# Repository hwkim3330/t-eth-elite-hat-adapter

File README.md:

# T-ETH-Elite ↔ Raspberry Pi HAT adapter

Hardware that lets a **Raspberry Pi HAT** run on a **LilyGO T-ETH-Elite**
(ESP32-S3) instead of a Pi. Built for one specific HAT — TSN Lab's
`10BASE-T1S HAT` (Microchip LAN8651, [devicemart #15980354](https://www.devicemart.co.kr/goods/view?no=15980354)),
which is a Pi-only product — so that a 10BASE-T1S node can be an ESP32 rather
than a Raspberry Pi. Firmware side lives in
[esp32-t1s-bridge](https://github.com/hwkim3330/esp32-t1s-bridge).

```
   TSN Lab 10Base-T1S HAT  (LAN8651)
   ── adapter PCB ──                    pcb/
   LilyGO T-ETH-Elite  (ESP32-S3)
   ── printed tray ──                   case/
```

| | |
|---|---|
| `pcb/` | the adapter board — KiCad project, gerbers, BOM/CPL |
| `case/` | printed base tray for the Elite, generated and clearance-checked by script |
| `reference/` | LilyGo's own DXF and 3D models, plus the script that re-derives every dimension from them |
| [`pcb/GEOMETRY.md`](pcb/GEOMETRY.md) | **the single source of truth** — every measured number, with its provenance |

## The short version of why this exists

Plugging the HAT straight onto the T-ETH-Elite *almost* works, and the two
reasons it doesn't are worth stating up front:

1. **Electrically it already works.** LilyGo wired the Elite's 40-pin header to
   the standard Raspberry Pi GPIO assignment, pin for pin. No level shifting,
   no remapping, nothing to translate. The adapter carries no signal logic at
   all — the connection is the stacking header's own pins, straight through.
2. **The near mounting holes already line up.** Deriving where a Pi's
   header-end holes must sit, from the Elite's own header position, lands on
   the Elite's own bottom hole pair to within **0.005 mm**. Same holes.
3. **But the RJ45 is in the way.** The Elite's RJ45 stands **15.97 mm** off the
   PCB while its header pins stop at **10.10 mm**. Any flat, un-notched board
   dropped onto that header — which is exactly what a standard Pi HAT is — hits
   the jack 5.87 mm before it seats. LilyGo's own shields cut a notch for it.
4. **And the far mounting holes fall off the end.** A HAT's far holes sit 49 mm
   from the near pair, i.e. at y = 53.63 in the Elite's frame — past the Elite's
   own board edge at 49.19. There is nothing there to screw into.

Of those, only (4) genuinely needs a board. A tall enough stacking header would
lift a HAT clear of the RJ45 on its own — so the honest claim is not "a HAT
cannot sit on this board", it is that without the adapter a HAT sits on **two
screws at the connector end and nothing at the other**, with the Elite's BOOT
and RESET switches buried underneath it. On a board you push terminal-block
levers into, that is the difference between a fixture and a wobble.

## Provenance

Nothing here was scaled off a drawing by eye. The mounting holes, the 40-pin
grid, the outline notches and the component heights all come out of LilyGo's own
published DXF and 3D CAD, cross-checked three ways — and the hole pattern was
independently validated against a real board on a laser-cut plate in
`~/stl-model/acrylic-frame`. `reference/measure.py` re-derives the whole set
from the vendor files, so the numbers can be audited rather than trusted:

```bash
pip install --user ezdxf trimesh manifold3d py7zr
python3 reference/measure.py
```

The one number that is *not* from CAD is the HAT's own 58 × 49 hole pattern,
which is inferred from a product photo (method and error bars in
[`pcb/GEOMETRY.md`](pcb/GEOMETRY.md)). Only the placement of the adapter's two far holes depends
on it.

## Status

Designed, checked, **never built**. No board has been fabricated, nothing has
been printed, and no part of the stack has been assembled or powered. The
clearance check the case script runs is against LilyGo's model, not against a
real board. Read the "not verified" sections in [`pcb/README.md`](pcb/README.md) and
[`case/README.md`](case/README.md) before spending money.

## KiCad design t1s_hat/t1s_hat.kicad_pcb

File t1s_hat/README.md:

# T1S HAT — LAN8651 10BASE-T1S for the LilyGO T-ETH-Elite

Our own 10BASE-T1S board for the [LilyGO
T-ETH-Elite](https://github.com/Xinyuan-LilyGO/LilyGO-T-ETH-Series)
(ESP32-S3), built around a **Microchip LAN8651** MAC-PHY. It replaces buying
TSN Lab's ready-made HAT: same chip, same host header, our schematic.

Two source files govern this board and **nothing here re-derives a number in
either of them**:

| file | governs |
|---|---|
| [`ELECTRICAL.md`](ELECTRICAL.md) | every component, value and pin-handling rule, each quoted from Microchip DS60001734F or AN1718 (DS60001718D) |
| [`../pcb/GEOMETRY.md`](../pcb/GEOMETRY.md) | outline, mounting holes, 2×20 grid — measured from LilyGo's own DXF and 3D CAD |

Everything is generated by [`make_t1s_hat.py`](make_t1s_hat.py), which emits
the symbol library, the two project-local footprints, the schematic and the
PCB, then reads the board back and asserts every mechanical feature against
`GEOMETRY.md`.

## What it is

- **LAN8651**, 32-VQFN 5×5, single 3.3 V rail (the '51 regulates its own 1.8 V
  core, so there is no second regulator and no sequencing diode).
- **OPEN Alliance TC6 SPI** to the host on the same header pins TSN Lab's
  device-tree overlay uses, so their SDK and the mainline `microchip,lan8651`
  driver both work unmodified if this board is ever put on a Pi.
- **Bus interface network** in AN1718's MINIMAL BIN order: common-mode choke →
  AC coupling caps → termination → ESD → 4-way 3.81 mm pluggable terminal
  block, wired so the node taps a daisy chain.
- 38 parts, 4 of them deliberately unstuffed. One of the 38 is a 0 Ω jumper,
  and it is a design decision, not an accident — see below.

## The two parts that had to be chosen, not assumed

Both are drawn from their own data sheet into
[`fp/t1s_hat.pretty`](fp/t1s_hat.pretty), generated by `make_t1s_hat.py`
alongside the board, and the generator asserts the pad count and the overall
land size back out of the finished `.kicad_pcb`.

### L1 — TDK **ACT1210L-201-2P-TL00**, LCSC **C131444**

AN1718 names ACT1210D-131-2P-TL00, ACT1210E-241-2P-TL00 and Murata
DLW32MH241MX2, and says in the same breath that *"exact component part numbers
and parameters must be determined by the customer's unique application
requirements"* — they are examples. All three are **3.2 × 2.5 mm** (EIA 1210)
2-line chokes in the 130…240 µH @ 100 kHz band. The board previously sat on
KiCad's `Inductor_SMD:L_CommonMode_Wurth_WE-CNSW-1206`, a **3.2 × 1.6 mm**
land: same length, 0.9 mm too narrow, so the real part's terminals miss the
pads. KiCad ships no 4-terminal common-mode choke land in 3225.

The part fitted instead is the **ACT1210L-201-2P-TL00**: same ACT1210 package,
200 µH @ 100 kHz — inside the span AN1718's own examples cover — 70 mA,
5.5 Ω, AEC-Q200, and, unlike all three examples, **stocked at LCSC**
(C131444, ~$0.39/1k), which is where this board gets built.

Its land is `t1s_hat:L_CommonMode_TDK_ACT1210_3225`, drawn from TDK's ACT1210
data sheet "Layout recommendation" (drawing IND1512-9): **4.1 mm overall
across the pads with a 2.0 mm gap between the columns**, so each pad is
1.05 mm long on a 3.05 mm pitch, and **1.6 mm overall across the rows with a
0.4 mm gap**, so each pad is 0.60 mm wide on a 1.0 mm pitch. Body from the
same sheet: 3.2 ±0.2 long, 2.5 ±0.2 wide, 3.9 max over the terminals.

The symbol changed with it: the ACT1210's windings are **1-4 and 2-3**
(pin configuration and circuit diagram, same sheet), which is
`Device:L_Coupled_1423`, not the `…_1243` the 1206 Würth part needed.

### MOV1 / MOV2 — TDK **AVRH10C221KT1R5YA8**, LCSC **C2157827**

This is the part `ELECTRICAL.md` already names, and it is a **1005 [0402]**
chip varistor — 1.0 × 0.5 × 0.5 mm, 220 V V1mA, 70 V DC, **1.5 pF**, 25 kV per
IEC 61000-4-2. The board had it on `Resistor_SMD:R_1206_3216Metric`: three
size codes too big. It is now on `t1s_hat:Varistor_TDK_AVRH10_1005`, from the
recommended land pattern in TDK's automotive AVR chip-varistor catalogue
(pad 0.35…0.45 long, gap 0.3…0.5, pad 0.4…0.6 wide — the middle of each:
**0.40 long, 0.40 gap, 0.50 wide**). KiCad's `R_0402_1005Metric` is 0.54 ×
0.64 on a 1.02 mm pitch, outside all three ranges, which is why this one is
drawn here too. Both parts stay **DNP**; the land is now a real one.

## Three decisions that are not in ELECTRICAL.md / GEOMETRY.md

These were directed after those files were written. They are marked
`DIRECTED:` in the generator, and the reasoning is recorded here.

### 1. Two layers, not four

`ELECTRICAL.md` calls 4 layers non-negotiable because AN1718 wants TRXP/TRXN
as length-matched, impedance-controlled 50 Ω single-ended traces, and 50 Ω on
2-layer 1.6 mm FR4 needs a ~2.9 mm trace. The width figure is right; the
conclusion does not follow at this speed and length. 10BASE-T1S runs at
12.5 MBd with deliberately slow, EMC-shaped edges, and the run from the QFN to
the connector here is ~20 mm — electrically short, well under the length at
which a mismatch on a trace this short costs anything at these edge rates.
AN1718's 50 Ω line is a "do this and you are safe" recommendation, not a
threshold this design crosses.

**So the impedance is not controlled and is not claimed to be.** The pair is
0.35 mm over 1.51 mm of FR4, which is nowhere near 50 Ω. What buys the margin
back instead is layout discipline, and those rules are treated as hard:

- **All signal routing is on F.Cu. B.Cu is an uninterrupted ground pour.**
  The generator asserts this — `verify()` counts B.Cu tracks and the table
  prints `B.Cu signals … 0 tracks`.
- The only two interruptions in that plane are the antenna keepout and the
  all-layer void under the choke, both of which AN1718 or the Elite requires,
  and the choke void is sized to the choke — see inference 8.
- The one crossing that a single signal layer could not absorb is a **0 Ω
  jumper on F.Cu**, not a via pair through the plane. See below.
- TRXP/TRXN are short, symmetric about x = 29.0 from the QFN to the connector,
  and carry **no vias**.

Moving to 4 layers with a dedicated reference plane is the fallback if EMC
measurements later ask for it. It is not a cost compromise.

### 2. No RJ45 notch — the outline is a plain rectangle

`GEOMETRY.md`'s notch exists because a board ~13 mm above the Elite would foul
the RJ45, which stands 15.97 mm. This board is lifted clear of the jack by a
taller riser instead, so nothing has to be cut away. Outline is the full
**66.22 × 49.19 mm rectangle, 3 mm corners**. Everything else mechanical in
`GEOMETRY.md` is unchanged and still authoritative: the four asymmetric
mounting holes and the 2×20 grid.

That is also what makes the 2-layer decision work — the notch was the largest
interruption in the bottom-side ground pour, right where the pair and its
choke want a clean reference.

### 3. The connection is two-stage — read this before ordering parts

```
   T1S HAT  (this board)
        ↑ its 2x20 socket goes on the riser's long pins
   ── 2x20 stacking riser ──          ≈18-20 mm total, set by the riser
        ↑ riser socket swallows the Elite's own 9.30 mm pins
        ↑ RJ45 (15.97 mm) passes beside the stack, not through a notch
   LilyGO T-ETH-Elite (ESP32-S3)
```

**A single tall stacking header does not work here.** The Elite's pins are
only 9.30 mm long; they would reach barely halfway up a ~17 mm barrel whose
contacts sit near the top. You need a **riser** (a 2×20 stacking header that
plugs onto the Elite and presents longer pins) plus this board's **socket**.
That is a real failure mode someone will otherwise hit at the checkout page.

Board height above the Elite PCB is **assumed ≈18–20 mm**, set by the riser.
Nothing on this board depends on the exact number.

## Stack-up assumed

JLCPCB's standard 2-layer 1.6 mm FR4 build, written into the board file:

| layer | | thickness |
|---|---|---|
| F.Cu | signals + GND flood | 0.035 mm (1 oz) |
| core | FR4, εr ≈ 4.5 | 1.510 mm |
| B.Cu | **ground plane, nothing else** | 0.035 mm (1 oz) |

Design rules: 0.15 mm minimum clearance and track, 0.45 mm minimum via
(0.25 mm drill), 0.20 mm minimum through-hole drill — the last one because the
stock `…_ThermalVias` QFN footprint uses 0.20 mm holes under the exposed pad.

## Termination stuffing — the one thing an assembler must decide

The board **ships with R1/R2 unstuffed**, per `ELECTRICAL.md` ("footprints
fitted, DNP by default — stuff per where this node sits on the bus"). The
silkscreen carries the table:

| where this node sits | R1, R2 |
|---|---|
| **end of the bus** | 49R9 1 % 1 W 1206 |
| **interior drop node** | 1K5 1 % 1206 |

`R3` (100 k) and `C3` (100 nF) — AN1718's common-mode termination — **are
fitted**. ESD elements MOV1/MOV2 have footprints and are DNP; `ELECTRICAL.md`
calls them optional.

`CN1` is wired **P N N P**, and the silkscreen carries that as a legend
(`CN1 1=P 2=N 3=N 4=P`) in the clear area to its left. Per-pad letters were
dropped: the four pads are 1.8 × 3.6 mm ovals with the connector's own body
outline 0.9 mm below them and R3/C3 0.6 mm below that, leaving a 0.6 mm slot —
nowhere to letter a pad without printing on copper. Pins 1–2 and 3–4 are the
same pair with opposite orientation, so wire P to P and N to N rather than
pin-for-pin. That order is what lets both on-board links be drawn without a
crossing.

## Verified

- **Mechanical: worst error 0.00000 mm** against `GEOMETRY.md`, tolerance
  0.01 mm, over the outline, all four mounting holes and all 40 header pads.
  `make_t1s_hat.py` prints the full table and exits non-zero on any failure.
- **Antenna keepout clean.** The generator walks every track, via, footprint
  and *filled zone polygon* on both layers and counts anything inside
  x 58…66.22, y 22…44: **0 intruders.** The keepout is a rule area that forbids
  copper, tracks, vias, pads and footprints on both layers, so both pours are
  cut out there. Silkscreen (ink, not copper) does mark the window.
- **B.Cu carries 0 signal tracks.**
- **Unrouted connections: 0.**
- **L1 and MOV1/MOV2 lands read back as 4.10 × 1.60 mm on 4 pads and
  1.20 × 0.50 mm on 2 pads** — the data sheet numbers above, asserted out of
  the board file, not just written into it.
- **ERC: 0 errors, 5 warnings** — see below.
- **DRC: 0 errors, 4 warnings** — see below.

### ERC — 0 errors

`kicad-cli` 7.0.11 has no `sch erc` subcommand, only `export`, so ERC is run
through the real eeschema on an Xvfb display by
[`run_erc.sh`](run_erc.sh), with **Show: All and Exclusions both ticked**
before the run. Report as produced: [`erc.rpt`](erc.rpt).

```
** ERC messages: 5  Errors 0  Warnings 5
```

All 5 warnings are the same thing: *"Pins of type Bidirectional and Power
output are connected"* on U1 pins 20, 22, 23 (DIOA2/3/4) and 16, 14
(DIOB0/DIOB1). Those are the unused configurable IO tied to ground, which is
exactly what the data sheet says to do — *"When not used, these pins may be
connected directly to ground."* Nothing is excluded or suppressed.

### DRC — 0 errors, 4 warnings

Run through `pcbnew.WriteDRCReport()` (same engine; `kicad-cli` has no
`pcb drc` either). Report as produced: [`drc.rpt`](drc.rpt).

```
** Found 4 DRC violations **
** Found 0 unconnected pads **
** Found 0 Footprint errors **
```

**Zero errors of any kind** — no clearance, hole, courtyard, keepout,
solder-mask, silkscreen or unconnected-pad violation. All four remaining
warnings are the same one:

| count | what |
|---|---|
| 4 | `lib_footprint_issues` — the four Ø2.75 mounting holes are generated inline and belong to no footprint library, so the library-consistency test has nothing to compare them to (same as `../pcb/`) |

Nothing is excluded. Running it yourself reproduces exactly this.

## Two crossings on one layer, and how they were closed

The host bundle is **not planar on one layer**. With the LAN8651's pin order
(IRQ 9, SDO 10, CS_N 11, SCLK 12, SDI 13, left to right along the QFN's bottom
edge) and `ELECTRICAL.md`'s header assignment (IRQ→16, MOSI→19, MISO→21,
SCLK→23, CS_N→24), SDI/MOSI starts at the right-hand end of the QFN and has to
reach the left-hand end of its target group, so it must cross the other four.
MOSI takes the long way round — out to x = 39.9, down, and back along a 2 mm
band under the header — which resolves that crossing, but the loop it traces
then encloses the CS_N column, and 3V3 enters the board outside that loop.
VDDP is fenced in the same way, by the +3V3 tree, the header row and the SPI
fan-out. That left one crossing on each of two nets.

**B.Cu was not used for either.** The uninterrupted bottom pour is the thing
buying back the fourth layer on this design; `B.Cu signal tracks: 0` is still
asserted by the generator and still true.

### `SPI_CS_N` — closed by moving R5, no new part

R5 (the 10 k CS_N pull-up) moved from (50, 12.4) to **(32.326, 9.5)**, where it
sits **astride the SPI_MISO column**: MISO runs vertically between R5's own two
pads. A 0603's pads are 0.85 mm apart, so a 0.25 mm track through the middle
keeps 0.30 mm to each — the textbook 2-layer crossover, except that the part
doing the hopping is one that had to be in the CS_N path anyway. Its 3V3 now
comes off the column that already feeds R6, and its CS_N leg lands straight on
the CS_N column. Cost: zero extra parts.

### `VDDP` — closed by JP1, a real 0 Ω jumper

There is no equivalent trick for VDDP: its two halves are both VDDP, and no
VDDP-to-VDDP part existed to hop with. So **JP1, a 0 Ω 0603, is fitted at
(6.9, 8.7)**, straddling the +3V3 branch that climbs the left edge — +3V3
passes between its pads. It is a real part, and it is real everywhere:

- in the schematic, as `Device:R`, with the net split either side of it
  (`VDDP` on the pin-7 island, **`VDDP_17`** on the pin-17 island, each with
  its own PWR_FLAG so ERC sees both as supplied);
- in [`bom.csv`](bom.csv) and [`cpl.csv`](cpl.csv), `Populate = fit`, described
  as *"FITTED — the board does not work without it"*;
- on the silkscreen, designator `JP1`, like every other part.

From JP1 the link runs round the outside of the header in the free ~1 mm lane
below it and climbs back between two pad columns at x = 42.486. Nothing else
goes under the header there: the +3V3 rail stops at y = 2.0 and MOSI's return
at y = 1.35, and both turn upward before that lane. It is a long way round —
the VDDP_17 net totals 84 mm of 0.30…0.45 mm track, about 0.1 Ω, ~3 mV at
50 mA — and each island keeps its own 0.1 µF + 0.01 µF at the pin, so the
length costs nothing that matters. **The short way round does not exist on one
layer**; the alternative was a via pair through the ground plane, which this
design does not spend.

## Silkscreen — 48 violations to 0

The silkscreen exists so the board can be assembled and debugged, and it was
not doing that job: designators sat on pads and on each other (`R3` across the
connector, `C1`/`C2` over pads, `MOV2` into `CN1`).

| | before | after |
|---|---|---|
| `silk_overlap` | 28 | **0** |
| `silk_over_copper` | 15 | **0** |
| `silk_edge_clearance` | 5 | **0** |
| designators dropped | — | **0 of 38** |

Library footprints put their reference wherever the library author did, which
on a board this dense is wherever the neighbour already is. They are placed by
the generator instead: `place_references()` tries each designator in a ring of
candidate positions around its own part — horizontal first, sideways only if
nothing horizontal fits — and keeps the first that clears every pad, via, ink
and the board edge. A part with nowhere legible left would lose its
designator rather than print an unreadable pile; in the end none had to.
Three positions are hinted (`J1`, `U1`, `R1`, `Y1`) because the ring around a
large or boxed-in part lands somewhere silly, and a hint still has to pass the
same clearance test as any other candidate.

Four other things moved with it:

- **Board text** was re-laid into the two areas that carry no pads — the strip
  left of the bus network and the top-right corner — and shortened to fit
  clear of CN1's body outline.
- **CN1's per-pad P/N letters** became one legend line; see above.
- **The J1 pin-1 marker** is a filled dot outboard of pin 1, not a stroked
  triangle above it. Above is where JP1 has to sit, and the triangle's three
  legs also overlapped *each other* at the apex — one filled shape cannot.
- **CN1 moved 0.35 mm inboard** (y 41 → 40.65): its body outline otherwise
  lands 0.02 mm from `Edge.Cuts`, and the keepout window's ink now stops
  0.32 mm short of the board edge instead of running onto it.

## Inferences — things not taken from the spec files

Flagged because they are judgement, not quotation:

1. **U1 pin 1 (INH) is left unconnected.** `ELECTRICAL.md`'s pin-handling
   table does not cover INH. DS60001734F Table 3-5 says *"When not used, this
   pin should be left unconnected"*, so it is, with no copper stub.
2. **L1 is a 200 µH part where AN1718's examples are 130 and 240 µH.**
   AN1718 gives no minimum or maximum, only three example part numbers and an
   instruction to pick for the application; 200 µH is inside the span they
   cover and is the value TDK itself lists for one-pair automotive Ethernet.
   The land pattern is quoted, not inferred — but the *choice of value inside
   that span* is judgement.
3. **The 0 Ω jumper JP1 and the net split `VDDP` / `VDDP_17`** are a layout
   decision, not something either spec file asks for. `ELECTRICAL.md` treats
   VDDP as one net; on this board it is one net with a 0 Ω link in it.
4. **The crystal is a 2-pin 3.2 × 1.5 mm package** (`Crystal_SMD_3215-2Pin`),
   not a 4-pin grounded-case one. `ELECTRICAL.md` specifies 25 MHz,
   fundamental, parallel, CL 18 pF and says nothing about the package; the
   2-pin part routes cleanly here. A grounded-case 3225 is better for EMC and
   is a footprint swap.
5. **XTI is declared `passive` in the LAN8651 symbol**, not `input`. It is an
   oscillator pin driven by a passive crystal; declaring it an input makes
   KiCad's `pin_not_driven` test fire on a net that has no driver by design.
   Common practice, but it is a choice.
6. **The 40-pin header is a project-local symbol**, `t1s_hat:HAT_HEADER_2x20`,
   not `Connector_Generic:Conn_02x20_Odd_Even`. Its pins carry real electrical
   types (the six host signals are `output`/`input`, everything else
   `passive`), because the ESP32 side really is the driver and the generic
   connector's all-passive pins make ERC report every SPI input as undriven.
   The **footprint** is the stock `PinHeader_2x20_P2.54mm_Vertical`.
7. **Header pin 1 is at the low-x end, odd pins on the y = 3.360 row.**
   Inherited from `../pcb/`, where it is derived (not measured) from the Pi
   convention and from USB_DN/DP on pins 35/37 routing to the Elite's
   right-hand USB-C. Affects silkscreen only.
8. **`BIN_VOID` = x 21…40.5, y 23.4…39.8** and **`CMC_VOID` = x 26.90…30.10,
   y 24.40…28.80.** AN1718 asks for "a void in the ground flooding on the
   outside layer surrounding the BIN" and "an all-layer void underneath the
   CMC" **without giving dimensions**, so both sizes are judgement. The first
   follows the BIN components. The second is the only place other than the
   antenna window where the B.Cu reference plane is cut, so it is sized to the
   part and no further: **the ACT1210's maximum body — 3.9 mm over the
   terminals × 2.7 mm wide (2.5 + tolerance) — plus 0.25 mm a side**, giving
   3.2 × 4.4 mm (L1 is rotated 90°, so the 3.9 runs along y). The margin
   covers placement tolerance and nothing else; the body is what couples to
   the plane, because the body is the core. That also covers the 4.1 × 1.6 mm
   land with room to spare. The void grew in x against the old number above,
   not because the margin grew but because the part did: the 1206 land it used
   to be sized around was the wrong part. C11/C12 moved 0.8 mm outboard so
   their ground vias stay clear of it.
9. **The T1S pair necks to 0.15 mm at the QFN.** The package puts TRXP and
   TRXN 0.5 mm apart; AN1718's "3× trace width centre-to-centre to other
   signals" cannot be met between the pair's own two legs at a 0.5 mm-pitch
   QFN, and Microchip's own EVB does not either. It **is** met against every
   other net, by the F.Cu void around the BIN.
10. **Pair length match ≈0.2 mm.** TRXN opens out to the choke before TRXP
    does (so the gap only ever grows), which costs about 0.2 mm of mismatch —
    roughly 1.2 ps. Not measured on hardware.
11. **The stackup numbers** (1.51 mm core, εr 4.5, 1 oz outer copper) are
    JLCPCB's standard 2-layer build, taken as the assumption, not measured.

## Files

| file | what |
|---|---|
| `ELECTRICAL.md` | **electrical source of truth** |
| `make_t1s_hat.py` | generator: symbol lib → schematic → PCB → verify → DRC → exports |
| `run_erc.sh` | runs eeschema's ERC headlessly (Xvfb + xdotool) and saves the report |
| `fill_zones.sh` | fills the zones through pcbnew's GUI — `ZONE_FILLER` segfaults in KiCad 7.0.11's Python bindings |
| `t1s_hat.kicad_sch` / `.kicad_pro` / `sym-lib-table` / `fp-lib-table` | schematic + project |
| `sym/t1s_hat.kicad_sym` | **LAN8651** (33 pins incl. the exposed pad) and the host header — neither exists in KiCad's libraries |
| `fp/t1s_hat.pretty/` | the TDK ACT1210 choke land and the TDK AVRH10 varistor land, each from that part's own data sheet — KiCad ships neither |
| `t1s_hat.kicad_pcb` | the board |
| `gerbers/t1s_hat_gerbers.zip` | fab-ready: 8 gerber layers, separate PTH/NPTH Excellon, drill maps, job file |
| `bom.csv` / `cpl.csv` | BOM (with a `Populate` column) and position file |
| `preview-front.png/.svg`, `preview-back.png/.svg` | both sides |
| `erc.rpt` / `drc.rpt` | reports as produced, nothing excluded |

Regenerate with `python3 make_t1s_hat.py`. Geometry is reproducible to the
internal unit, but the output is not byte-reproducible — KiCad stamps fresh
UUIDs and timestamps on every run. Compare the printed coordinate table, not
the files.

Drill files and `cpl.csv` are plotted against the drill/place origin, which the
generator puts on `GEOMETRY.md`'s own origin, so `NPTH.drl` literally reads
`X3.33Y4.63` and `cpl.csv` reads `8.196, 3.360`.

## Bottom side — clear area for a later variant

The board now sits ~18–20 mm above the Elite, so **the bottom is usable**:

| region | clearance below |
|---|---|
| everywhere except the RJ45 footprint | ≈14 mm or more |
| over the RJ45, x −5.18…16.42, y 10.50…28.90 | **much less** — the jack tops out at 15.17 mm above the Elite's PCB |
| under the 2×20 socket, y 0…9 | occupied by the socket body |

Nothing is placed on B.Cu on this board (it is the ground plane). A radar
variant wanting that space should stay clear of the RJ45 column and of the
header, and must not slot the plane under the bus pair.

## What is NOT verified — read before ordering

- **Nothing has been bench-tested.** No board, no Elite, no riser in hand.
- **The two project-local lands are transcribed from data sheets, not
  measured.** L1's came from TDK's ACT1210 layout recommendation and MOV's
  from TDK's AVR catalogue; the generator asserts that what is in the board
  file matches what was transcribed, which is not the same as asserting that
  the transcription is right. Both are worth one look at the PDF before fab —
  they are the only two lands here that KiCad did not supply.
- **LCSC stock and part status were read from the catalogue, not ordered
  against.** C131444 (L1) and C2157827 (MOV1/2) were in stock when this was
  written; neither is confirmed as a JLCPCB *basic* part, so expect an
  extended-part fee or hand-placement for L1.
- **Impedance is not controlled** and the 50 Ω figure in `ELECTRICAL.md` is
  deliberately not met; see the 2-layer decision.
- **Oscillator margin was not calculated.** `ELECTRICAL.md` asks for >10; that
  depends on the crystal's ESR and C0, which are not fixed to a part number.
- **The riser is specified by class, not part number**, and it sets the stack
  height. Pick it before the standoffs.
- **No order was placed.** The deliverable is fab-ready files to upload.

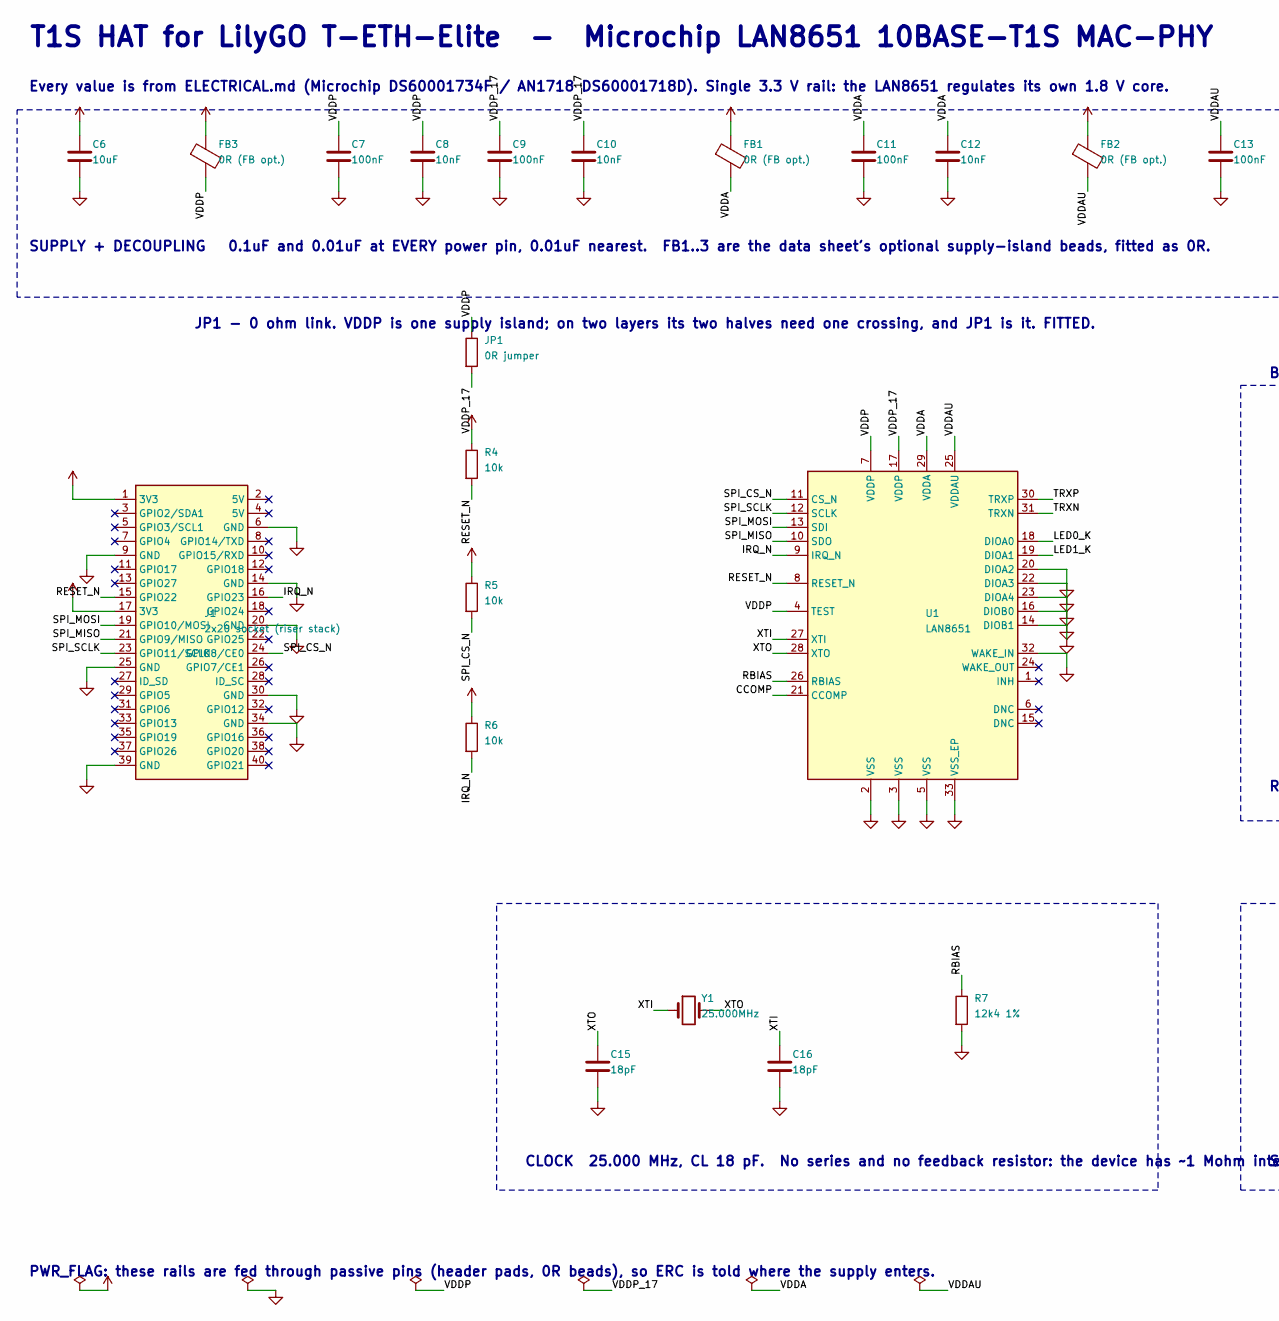
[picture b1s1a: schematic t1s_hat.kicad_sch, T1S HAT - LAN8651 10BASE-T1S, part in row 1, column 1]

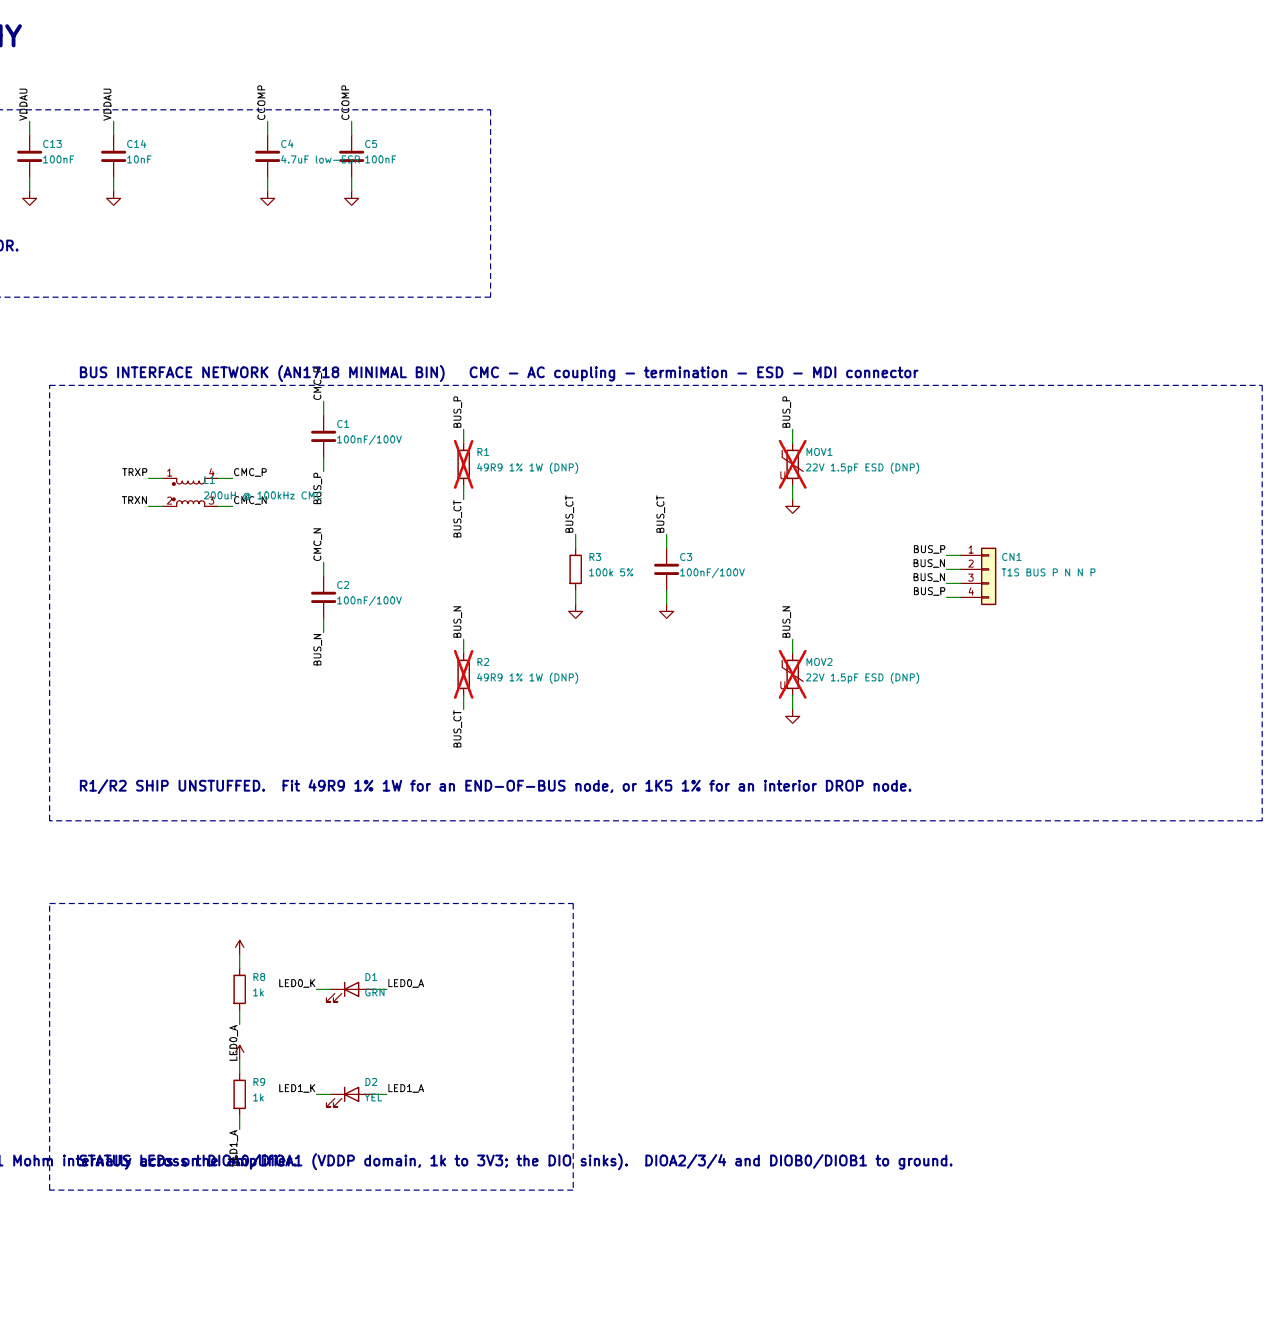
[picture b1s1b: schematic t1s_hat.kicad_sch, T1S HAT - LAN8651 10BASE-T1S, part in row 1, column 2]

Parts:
C1, C2, C3: 100nF/100V; C_0805_2012Metric
C4: 4.7uF low-ESR; C_0805_2012Metric
C5, C7, C9, C11, C13: 100nF; C_0603_1608Metric
C6: 10uF; C_0805_2012Metric
C8, C10, C12, C14: 10nF; C_0603_1608Metric
C15, C16: 18pF; C_0603_1608Metric
CN1: T1S BUS P N N P; PhoenixContact_MC_1,5_4-G-3.81_1x04_P3.81mm_Horizontal
D1: GRN; LED_0603_1608Metric
D2: YEL; LED_0603_1608Metric
FB1, FB2, FB3: 0R (FB opt.); L_0603_1608Metric
J1: 2x20 socket (riser stack); PinHeader_2x20_P2.54mm_Vertical
JP1: 0R jumper; R_0603_1608Metric
L1: 200uH @ 100kHz CMC; L_CommonMode_TDK_ACT1210_3225; LCSC C131444
MOV1, MOV2: 22V 1.5pF ESD (DNP); Varistor_TDK_AVRH10_1005; LCSC C2157827; not fitted
R1, R2: 49R9 1% 1W (DNP); R_1206_3216Metric; not fitted
R3: 100k 5%; R_0805_2012Metric
R4, R5, R6: 10k; R_0603_1608Metric
R7: 12k4 1%; R_0603_1608Metric
R8, R9: 1k; R_0603_1608Metric
U1: LAN8651; TQFN-32-1EP_5x5mm_P0.5mm_EP3.4x3.4mm_ThermalVias
Y1: 25.000MHz; Crystal_SMD_3215-2Pin_3.2x1.5mm

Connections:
+3V3: C6.1, FB1.1, FB2.1, FB3.1, J1.1 (3V3), J1.17 (3V3), R4.1, R5.1, R6.1, R8.1, R9.1
BUS_CT: C3.1, R1.2, R2.2, R3.1
BUS_N: C2.2, CN1.2, CN1.3, MOV2.1, R2.1
BUS_P: C1.2, CN1.1, CN1.4, MOV1.1, R1.1
CCOMP: C4.1, C5.1, U1.21 (CCOMP)
CMC_N: C2.1, L1.3
CMC_P: C1.1, L1.4
GND: C3.2, C4.2, C5.2, C6.2, C7.2, C8.2, C9.2, C10.2, C11.2, C12.2, C13.2, C14.2, C15.2, C16.2, J1.6 (GND), J1.9 (GND), J1.14 (GND), J1.20 (GND), J1.25 (GND), J1.30 (GND), J1.34 (GND), J1.39 (GND), MOV1.2, MOV2.2, R3.2, R7.2, U1.2 (VSS), U1.3 (VSS), U1.5 (VSS), U1.14 (DIOB1), U1.16 (DIOB0), U1.20 (DIOA2), U1.22 (DIOA3), U1.23 (DIOA4), U1.32 (WAKE_IN), U1.33 (VSS_EP)
IRQ_N: J1.16 (GPIO23), R6.2, U1.9 (IRQ_N)
LED0_A: D1.2 (A), R8.2
LED0_K: D1.1 (K), U1.18 (DIOA0)
LED1_A: D2.2 (A), R9.2
LED1_K: D2.1 (K), U1.19 (DIOA1)
RBIAS: R7.1, U1.26 (RBIAS)
RESET_N: J1.15 (GPIO22), R4.2, U1.8 (RESET_N)
SPI_CS_N: J1.24 (GPIO8/CE0), R5.2, U1.11 (CS_N)
SPI_MISO: J1.21 (GPIO9/MISO), U1.10 (SDO)
SPI_MOSI: J1.19 (GPIO10/MOSI), U1.13 (SDI)
SPI_SCLK: J1.23 (GPIO11/SCLK), U1.12 (SCLK)
TRXN: L1.2, U1.31 (TRXN)
TRXP: L1.1, U1.30 (TRXP)
VDDA: C11.1, C12.1, FB1.2, U1.29 (VDDA)
VDDAU: C13.1, C14.1, FB2.2, U1.25 (VDDAU)
VDDP: C7.1, C8.1, FB3.2, JP1.1, U1.4 (TEST), U1.7 (VDDP)
VDDP_17: C9.1, C10.1, JP1.2, U1.17 (VDDP)
XTI: C16.1, U1.27 (XTI), Y1.1
XTO: C15.1, U1.28 (XTO), Y1.2

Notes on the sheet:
T1S HAT for LilyGO T-ETH-Elite - Microchip LAN8651 10BASE-T1S MAC-PHY
Every value is from ELECTRICAL.md (Microchip DS60001734F / AN1718 DS60001718D). Single 3.3 V rail: the LAN8651 regulates its own 1.8 V core.
SUPPLY + DECOUPLING 0.1uF and 0.01uF at EVERY power pin, 0.01uF nearest. FB1..3 are the data sheet's optional supply-island beads, fitted as 0R.
JP1 - 0 ohm link. VDDP is one supply island; on two layers its two halves need one crossing, and JP1 is it. FITTED.
BUS INTERFACE NETWORK (AN1718 MINIMAL BIN) CMC - AC coupling - termination - ESD - MDI connector
R1/R2 SHIP UNSTUFFED. Fit 49R9 1% 1W for an END-OF-BUS node, or 1K5 1% for an interior DROP node.
CLOCK 25.000 MHz, CL 18 pF. No series and no feedback resistor: the device has ~1 Mohm internally across the amplifier.
STATUS LEDs on DIOA0/DIOA1 (VDDP domain, 1k to 3V3; the DIO sinks). DIOA2/3/4 and DIOB0/DIOB1 to ground.
PWR_FLAG: these rails are fed through passive pins (header pads, 0R beads), so ERC is told where the supply enters.

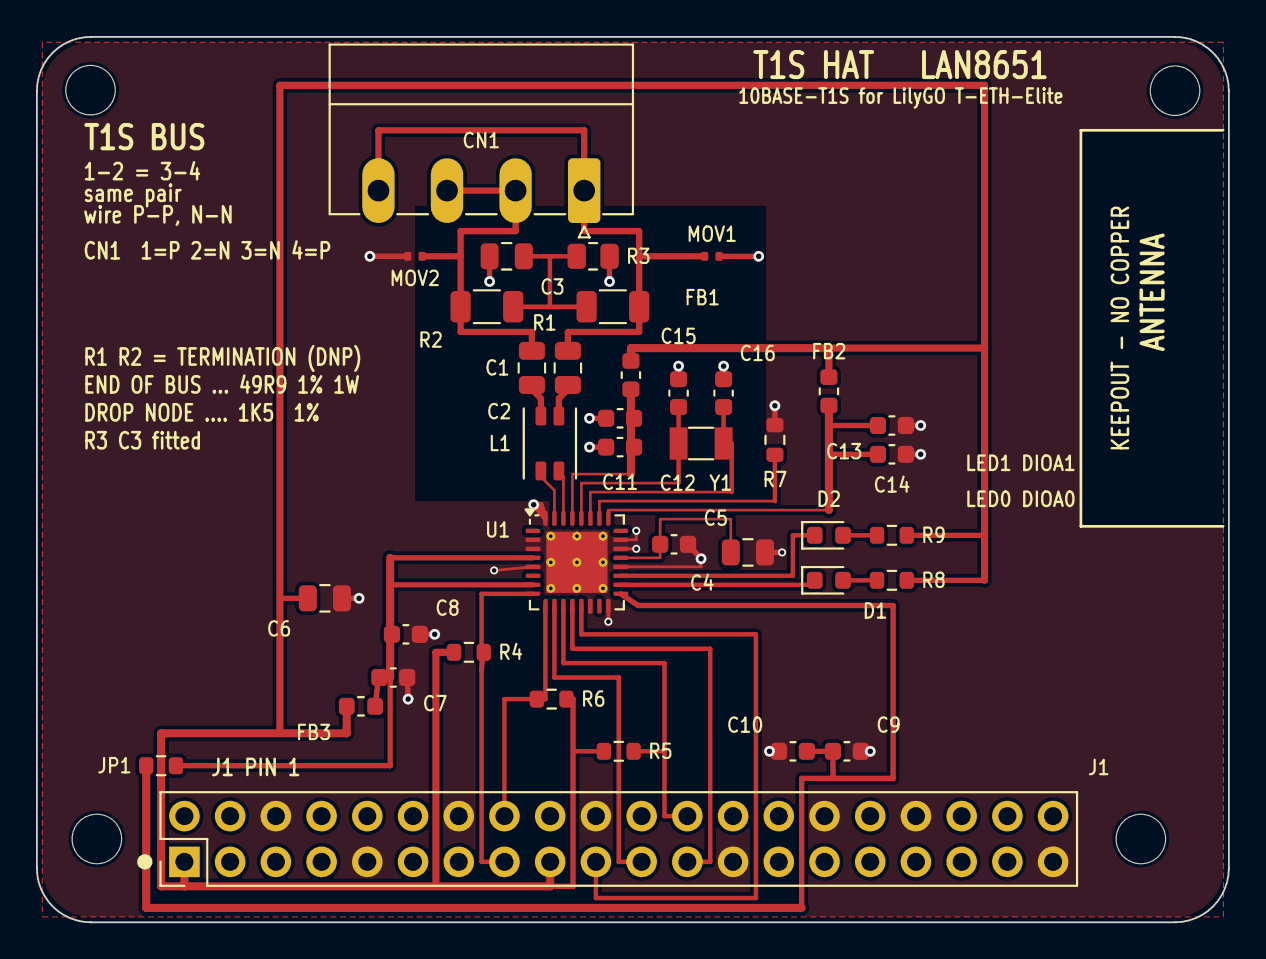
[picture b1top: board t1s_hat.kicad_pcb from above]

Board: 2 copper layers, 66.2 x 49.2 mm, 42 parts (0 on the bottom side), 27 nets.

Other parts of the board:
H1, H2, H3, H4: NPTH_2.75mm

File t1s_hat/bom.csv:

Comment,Designator,Footprint,Quantity,Populate,Description,LCSC
100nF/100V,C1,Capacitor_SMD:C_0805_2012Metric,1,fit,"AC coupling / galvanic isolation, bus P. ALWAYS FITTED (AN1718)",
10nF,C10,Capacitor_SMD:C_0603_1608Metric,1,fit,"VDDP (pin 17) decoupling, 0.01 uF - closest to the pin",
100nF,C11,Capacitor_SMD:C_0603_1608Metric,1,fit,"VDDA (pin 29) decoupling, 0.1 uF",
10nF,C12,Capacitor_SMD:C_0603_1608Metric,1,fit,"VDDA (pin 29) decoupling, 0.01 uF - closest to the pin",
100nF,C13,Capacitor_SMD:C_0603_1608Metric,1,fit,"VDDAU (pin 25) decoupling, 0.1 uF",
10nF,C14,Capacitor_SMD:C_0603_1608Metric,1,fit,"VDDAU (pin 25) decoupling, 0.01 uF - closest to the pin",
18pF,C15,Capacitor_SMD:C_0603_1608Metric,1,fit,Crystal load capacitor C1 (data sheet: C1 = C2 = 18 pF),
18pF,C16,Capacitor_SMD:C_0603_1608Metric,1,fit,Crystal load capacitor C2 (data sheet: C1 = C2 = 18 pF),
100nF/100V,C2,Capacitor_SMD:C_0805_2012Metric,1,fit,"AC coupling / galvanic isolation, bus N. ALWAYS FITTED (AN1718)",
100nF/100V,C3,Capacitor_SMD:C_0805_2012Metric,1,fit,"Common-mode termination, centre tap to ground (AN1718 C3)",
4.7uF low-ESR,C4,Capacitor_SMD:C_0805_2012Metric,1,fit,"CCOMP: internal +1.8 V core LDO compensation. REQUIRED, low ESR, to the ground plane (LAN8651 only).",
100nF,C5,Capacitor_SMD:C_0603_1608Metric,1,fit,"CCOMP support capacitor (data sheet: useful, not required)",
10uF,C6,Capacitor_SMD:C_0805_2012Metric,1,fit,Bulk decoupling on the 3.3 V supply side,
100nF,C7,Capacitor_SMD:C_0603_1608Metric,1,fit,"VDDP (pin 7) decoupling, 0.1 uF",
10nF,C8,Capacitor_SMD:C_0603_1608Metric,1,fit,"VDDP (pin 7) decoupling, 0.01 uF - closest to the pin",
100nF,C9,Capacitor_SMD:C_0603_1608Metric,1,fit,"VDDP (pin 17) decoupling, 0.1 uF",
T1S BUS  P N N P,CN1,"Connector_Phoenix_MC:PhoenixContact_MC_1,5_4-G-3.81_1x04_P3.81mm_Horizontal",1,fit,"MDI connector, 4-pin 3.81 mm pluggable terminal block. Pins 1..4 = P N N P; the two P and the two N are shorted on board so the node taps a daisy chain.",
GRN,D1,LED_SMD:LED_0603_1608Metric,1,fit,Status LED 0 on DIOA0 - firmware maps it (e.g. PLCA status),
YEL,D2,LED_SMD:LED_0603_1608Metric,1,fit,Status LED 1 on DIOA1 - firmware maps it (e.g. activity),
0R (FB opt.),FB1,Inductor_SMD:L_0603_1608Metric,1,fit,VDDA supply island option: 0 ohm fitted; may be replaced by a ~300 ohm @ 100 MHz bead (e.g. Wuerth 742792640).,
0R (FB opt.),FB2,Inductor_SMD:L_0603_1608Metric,1,fit,VDDAU supply island option: 0 ohm fitted.,
0R (FB opt.),FB3,Inductor_SMD:L_0603_1608Metric,1,fit,VDDP supply island option: 0 ohm fitted.,
2x20 socket (riser stack),J1,Connector_PinHeader_2.54mm:PinHeader_2x20_P2.54mm_Vertical,1,fit,2x20 2.54 mm THT socket; mates with the riser that plugs onto the T-ETH-Elite's own 9.30 mm header pins,
0R jumper,JP1,Resistor_SMD:R_0603_1608Metric,1,fit,"0 ohm link, VDDP pin-7 island to VDDP pin-17 island. The 2-layer crossover for +3V3, which passes between its pads. FITTED - the board does not work without it.",
200uH @ 100kHz CMC,L1,t1s_hat:L_CommonMode_TDK_ACT1210_3225,1,fit,"Common-mode choke, 2-line, 200 uH @ 100 kHz, EIA 1210 (3.2x2.5 mm), AEC-Q200 - TDK ACT1210L-201-2P-TL00 (AN1718 L1). ALWAYS FITTED.",C131444
22V 1.5pF ESD (DNP) [DNP],MOV1,t1s_hat:Varistor_TDK_AVRH10_1005,1,DNP,"ESD element on bus P, at the connector (AN1718 MOV1) - TDK AVRH10C221KT1R5YA8 chip varistor, 1005 [0402], 1.5 pF. Optional.",C2157827
22V 1.5pF ESD (DNP) [DNP],MOV2,t1s_hat:Varistor_TDK_AVRH10_1005,1,DNP,"ESD element on bus N, at the connector (AN1718 MOV2) - TDK AVRH10C221KT1R5YA8 chip varistor, 1005 [0402], 1.5 pF. Optional.",C2157827
49R9 1% 1W (DNP) [DNP],R1,Resistor_SMD:R_1206_3216Metric,1,DNP,"Bus termination, P leg. 49R9 1% 1W for an END node, 1K5 1% for a DROP node. Shipped unstuffed - see README.",
49R9 1% 1W (DNP) [DNP],R2,Resistor_SMD:R_1206_3216Metric,1,DNP,"Bus termination, N leg. 49R9 1% 1W for an END node, 1K5 1% for a DROP node. Shipped unstuffed - see README.",
100k 5%,R3,Resistor_SMD:R_0805_2012Metric,1,fit,"Common-mode termination, centre tap to ground (AN1718 R3)",
10k,R4,Resistor_SMD:R_0603_1608Metric,1,fit,RESET_N pull-up: a floating host GPIO during ESP32 boot must not hold the PHY in reset,
10k,R5,Resistor_SMD:R_0603_1608Metric,1,fit,"SPI CS_N pull-up; also the F.Cu crossover for SPI_MISO, which passes between its pads",
10k,R6,Resistor_SMD:R_0603_1608Metric,1,fit,IRQ_N pull-up (open-drain capable interrupt output),
12k4 1%,R7,Resistor_SMD:R_0603_1608Metric,1,fit,RBIAS. 12.4 kohm 1% over the whole operating temperature range - no substitutions (data sheet).,
1k,R8,Resistor_SMD:R_0603_1608Metric,1,fit,LED0 series resistor to 3V3 (DIOA0 sinks),
1k,R9,Resistor_SMD:R_0603_1608Metric,1,fit,LED1 series resistor to 3V3 (DIOA1 sinks),
LAN8651,U1,Package_DFN_QFN:TQFN-32-1EP_5x5mm_P0.5mm_EP3.4x3.4mm_ThermalVias,1,fit,"Microchip LAN8651 10BASE-T1S MAC-PHY, OPEN Alliance TC6 SPI, 32-VQFN 5x5 (internal 1.8 V core LDO -> single 3.3 V rail)",
25.000MHz,Y1,Crystal:Crystal_SMD_3215-2Pin_3.2x1.5mm,1,fit,"25.000 MHz fundamental parallel-resonant crystal, CL 18 pF, low ESR. No series or feedback resistor (data sheet).",
